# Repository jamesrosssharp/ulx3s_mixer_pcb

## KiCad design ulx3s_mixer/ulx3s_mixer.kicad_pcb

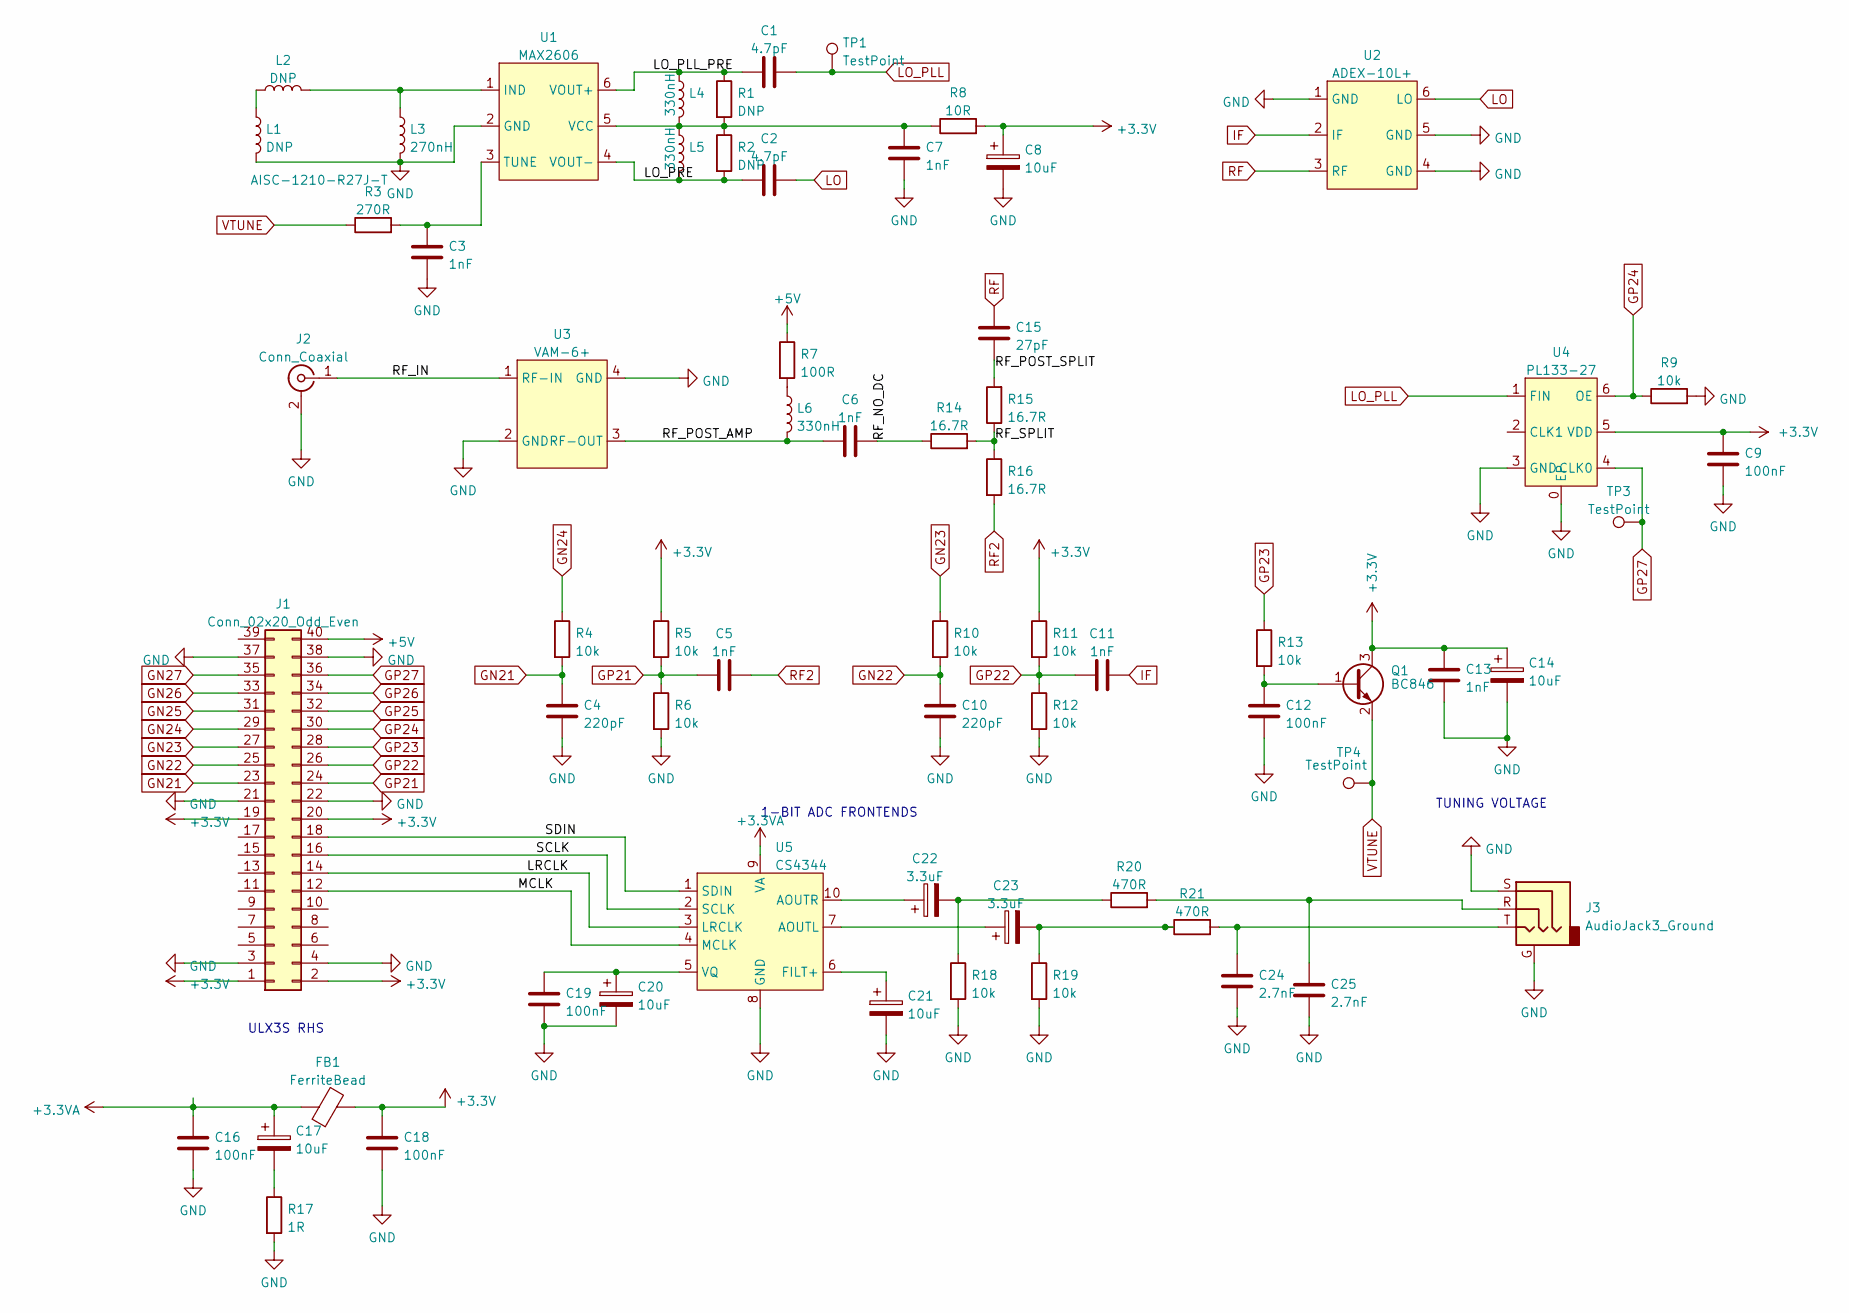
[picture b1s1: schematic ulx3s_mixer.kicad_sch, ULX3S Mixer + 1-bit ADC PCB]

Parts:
C1, C2: 4.7pF; C_0603_1608Metric; MPN RF18N4R7B500CT
C3, C5, C6, C7, C11, C13: 1nF; C_0603_1608Metric; MPN HH18N102J500CT
C4, C10: 220pF; C_0603_1608Metric; MPN 885382206001
C8, C14, C17, C20, C21: 10uF; C_1210_3225Metric; MPN CL32A106KOJNNNE
C9, C12, C16, C18, C19: 100nF; C_0603_1608Metric; MPN C0603C104K8RACTU
C15: 27pF; C_0603_1608Metric; MPN RF18N270J500CT
C22, C23: 3.3uF; C_1210_3225Metric; MPN CL31B335KOHNNNE
C24, C25: 2.7nF; C_0603_1608Metric; MPN 0603B272K500CT
FB1: FerriteBead; L_0402_1005Metric; MPN MMZ1005S601CT000
J1: Conn_02x20_Odd_Even; PinHeader_2x20_P2.54mm_Vertical; MPN DNP
J2: Conn_Coaxial; SMA_Amphenol_132289_EdgeMount; MPN CONSMA020.062-G
J3: AudioJack3_Ground; Jack_3.5mm_CUI_SJ-3523-SMT_Horizontal; MPN SJ-3523-SMT-TR
L1, L2: DNP; L_1210_3225Metric; MPN DNP
L3: 270nH; L_1210_3225Metric; MPN AISC-1210-R27J-T
L4, L5, L6: 330nH; L_1210_3225Metric; MPN AISC-1210-R33J-T
Q1: BC846; SOT-23; MPN BC846-T
R1, R2: DNP; R_0603_1608Metric; MPN DNP
R3: 270R; R_0603_1608Metric; MPN RMCF0603JT270R
R4, R5, R6, R9, R10, R11, R12, R13, R18, R19: 10k; R_0603_1608Metric; MPN 0603WAJ0103T5E
R7: 100R; R_0805_2012Metric; MPN CR0603-JW-101ELF
R8: 10R; R_0603_1608Metric; MPN RC0603FR-10510RL
R14, R15, R16: 16.7R; R_0603_1608Metric; MPN RT0603BRD0716R7L
R17: 1R; R_0603_1608Metric; MPN WR06W1R00FTL
R20, R21: 470R; R_0603_1608Metric; MPN 652-CR0603JW-471ELF
TP1, TP3, TP4: TestPoint; TestPoint_Pad_1.0x1.0mm; MPN DNP
U1: MAX2606; TSOT-23-6_HandSoldering; MPN MAX2606EUT+T
U2: ADEX-10L+; MPN ADEX-10L+
U3: VAM-6+; SOT-143-Weird; MPN VAM-6+
U4: PL133-27; TDFN2013-6LD-PL-1; MPN PL133-27GC-R
U5: CS4344; TSSOP-10_3x3mm_P0.5mm; MPN CS4344-CZZR

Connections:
+3.3VA: C16.1, C17.1, FB1.1, U5.9 (VA)
+3V3: C8.1, C9.1, C13.2, C14.1, C18.1, FB1.2, J1.1, J1.2, J1.19, J1.20, Q1.3 (C), R5.1, R8.2, R11.1, U4.5 (VDD)
+5V: J1.40, R7.1
/LO_PLL_PRE: C1.1, L4.1, R1.1, U1.6 (VOUT+)
/LO_PRE: C2.1, L5.2, R2.2, U1.4 (VOUT-)
/LRCLK: J1.14, U5.3 (LRCLK)
/MCLK: J1.12, U5.4 (MCLK)
/RF_IN: J2.1 (In), U3.1 (RF-IN)
/RF_NO_DC: C6.2, R14.1
/RF_POST_AMP: C6.1, L6.2, U3.3 (RF-OUT)
/RF_POST_SPLIT: C15.1, R15.2
/RF_SPLIT: R14.2, R15.1, R16.1
/SCLK: J1.16, U5.2 (SCLK)
/SDIN: J1.18, U5.1 (SDIN)
GN21: C4.1, J1.23, R4.2
GN22: C10.1, J1.25, R10.2
GN23: J1.27, R10.1
GN24: J1.29, R4.1
GN25: J1.31
GN26: J1.33
GN27: J1.35
GND: C3.2, C4.2, C7.2, C8.2, C9.2, C10.2, C12.2, C13.1, C14.2, C16.2, C18.2, C19.2, C20.2, C21.2, C24.1, C25.1, J1.3, J1.4, J1.21, J1.22, J1.37, J1.38, J2.2 (Ext), J3.G, J3.S, L1.2, L3.2, R6.2, R9.2, R12.2, R17.2, R18.2, R19.2, U1.2 (GND), U2.1 (GND), U2.4 (GND), U2.5 (GND), U3.2 (GND), U3.4 (GND), U4.0 (EP), U4.3 (GND), U5.8 (GND)
GP21: C5.1, J1.24, R5.2, R6.1
GP22: C11.1, J1.26, R11.2, R12.1
GP23: J1.28, R13.1
GP24: J1.30, R9.1, U4.6 (OE)
GP25: J1.32
GP26: J1.34
GP27: J1.36, TP3.1, U4.4 (CLK0)
IF: C11.2, U2.2 (IF)
LO: C2.2, U2.6 (LO)
LO_PLL: C1.2, TP1.1, U4.1 (FIN)
unnamed: C3.1, R3.2, U1.3 (TUNE)
unnamed: C7.1, L4.2, L5.1, R1.2, R2.1, R8.1, U1.5 (VCC)
unnamed: C12.1, Q1.1 (B), R13.2
unnamed: C17.2, R17.1
unnamed: C19.1, C20.1, U5.5 (VQ)
unnamed: C21.1, U5.6 (FILT+)
unnamed: C22.1, U5.10 (AOUTR)
unnamed: C22.2, R18.1, R20.1
unnamed: C23.1, U5.7 (AOUTL)
unnamed: C23.2, R19.1, R21.1
unnamed: C24.2, J3.T, R21.2
unnamed: C25.2, J3.R, R20.2
unnamed: L1.1, L2.1
unnamed: L2.2, L3.1, U1.1 (IND)
unnamed: L6.1, R7.2
RF: C15.2, U2.3 (RF)
RF2: C5.2, R16.2
VTUNE: Q1.2 (E), R3.1, TP4.1

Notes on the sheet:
ULX3S RHS
TUNING VOLTAGE
1-BIT ADC FRONTENDS

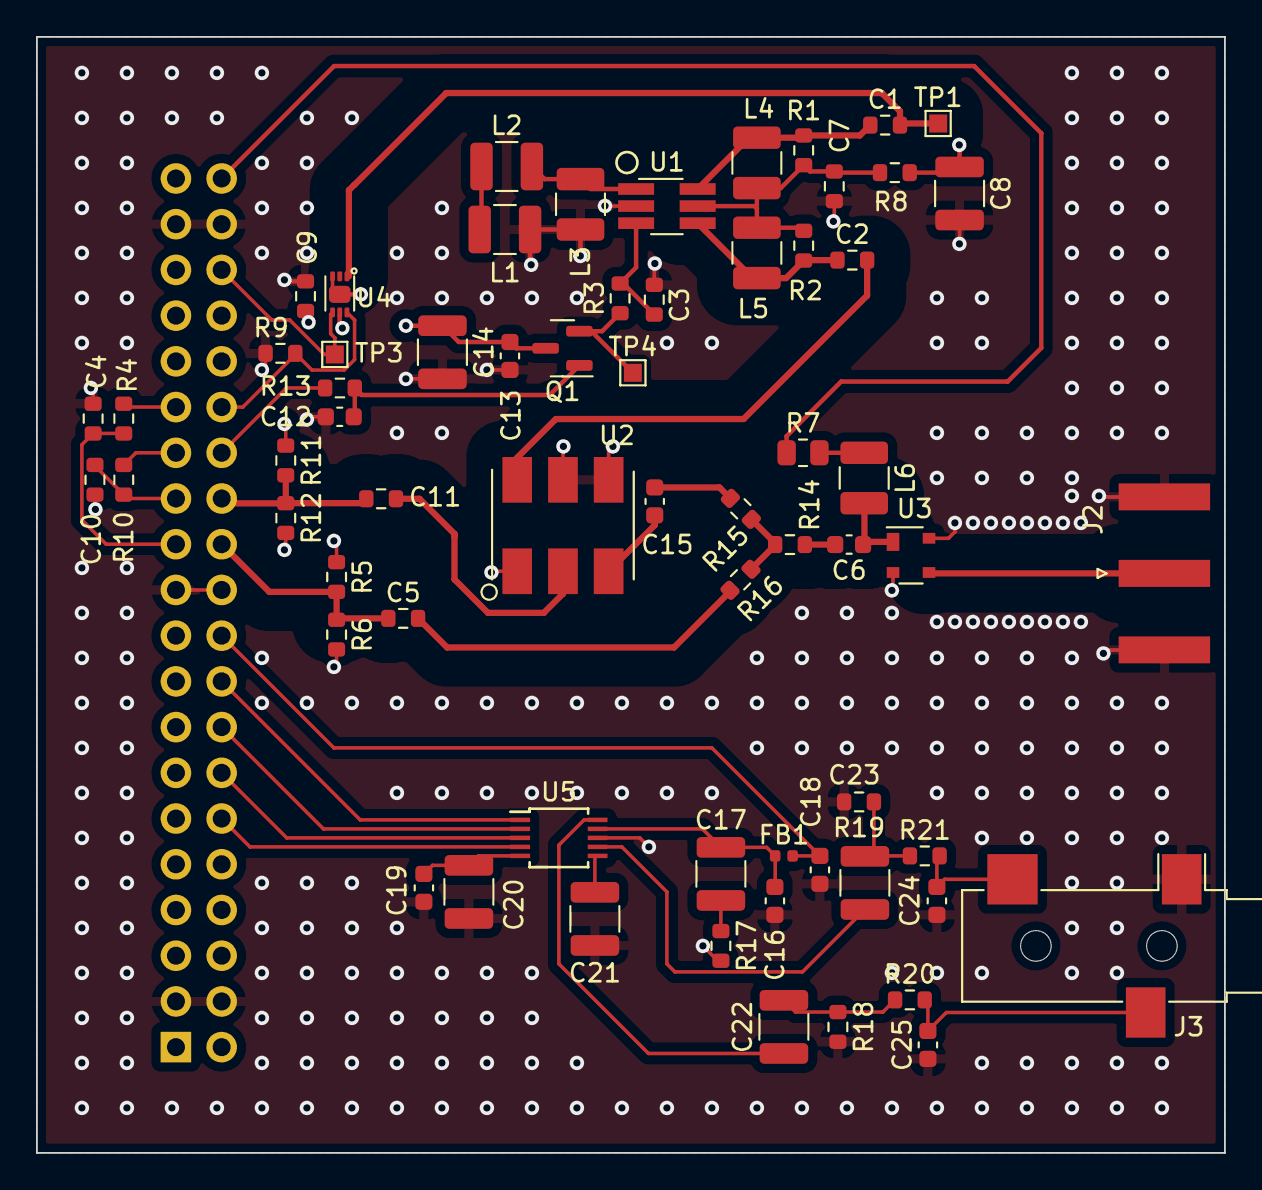
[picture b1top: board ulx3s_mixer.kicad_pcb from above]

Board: 4 copper layers, 66.0 x 62.0 mm, 65 parts (1 on the bottom side), 45 nets.

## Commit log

2024-06-16 Added all part numbers
2024-06-17 Added design rules and poly pour (zone) on top layer
2024-06-28 Added start of CS4344
2024-06-30 Finished CS4344 symbol
2024-06-30 Added CS4344 to schematic
2024-07-06 Finished design, exported BOM + gerbers
2024-07-06 Rejigged soldermask clearance and regnereated fab outputs
2024-08-17 Added start of HDL project
2024-08-17 Added audio CIC and FM demod
2024-08-18 Made audio quality slightly better and added VU meters
2024-08-20 Added deemphasis
2024-08-20 Fixed bug in lookup table
2024-08-24 Added 19kHz bandpass filter
2024-08-25 Added 19kHz bandpass filter, fixed atan2 table bug, extract pilot tone
2024-08-25 Added start of DPLL
2024-08-25 Added stereo demux
